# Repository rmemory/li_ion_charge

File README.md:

This repo contains the schematic and PCB layout for a battery charge controller board. 

The intent of this board is to provide a simple controller to connect a USB port to a discrete single cell recharagable Lithum Ion battery. The USB port will be used to provide power input only (~4.5v), and consequently the USB data port will not be used. This board will also be capable of providing power to a CPU board (3.3V). 

The charge controller chip selected for this board is the Microchip MCP73834. The 834 has been selected due to the optional timer functionality over the 833. The timer provides some protection to no unmonitored, unattended charging over a long period of time.

http://ww1.microchip.com/downloads/en/DeviceDoc/22005a.pdf

Its benefits include the following:

* This chip adhers to all of the power standards of the USB bus and also intended primarily to charge a lithium ion battery.

* Integrated pass (controlling) transistor. This has the advantage of not requiring a seperate external discrete part. The potential slight disadvantage of not being able to control the exact characteristics of the transistor are not a problem in this particular case.

* Integrated current sense.

* The reverse discharge protection feature is nice but in this case not a priority because only a USB connector input (4.2 - 4.5v) will be supported as opposed to two open wires (which in theory could be connected to anything allowing the battery to be discharged).

* Preconditioning of a deeply discharged battery is another nice feature to prevent overheating (and fire!) of the battery during recharge. If a Li-ion battery is deeply discharged (for example, to below 3 V) a small “pre-conditioning” charge of around 10% of the full-charge current is applied. This prevents the cell from overheating until such a time that it is able to accept the full current of the constant-current phase. In reality, this phase is rarely needed because most modern mobile devices are designed to shut down while there’s still some charge left because deep discharge, like overcharging, can damage the cell. With that said, note the external heat sensing thermistor is not used in this design.

* The sample application circuit specified in the data sheet will be used with minor modifications.

* A linear drop out mode is also useful as the internal resistance of the battery increases and battery output voltage degrades.

* The MSOP 10 package will be used to allow for hand soldering.

A designer's guide to lithium battery charging can be found here:

https://www.digikey.com/en/articles/techzone/2016/sep/a-designer-guide-fast-lithium-ion-battery-charging

Circut design notes:
======================

The "typical application" circuit provided on the data sheet will provide the core of the circuit design.

A regulated current of 500 mA will be used, and thus according to the equation Ireg = 1000V/Rprog, a value of 2k ohms for the Rprog will be used.

A standard USB Type A connector will be used. 

A slightly larger 4.7 uF capacitor, with a 1206 foot print will be used to accomodate for the 500 mA charging current. The 4.7 uF caps are available in an 0805 size, but they tend to be more expensive and more difficuclt to find.

Rudimentary reset functionality will be provided via a jumper.

Via Stitching (i.e. adding of extra vias between planes) reduces inductance between planes. All conductors have some inductance due to the magnetic field due to the current flowing. The inductance will increase as signal frequency increases. For example, a square wave (data) has many high frequency signals. One via will create a small inductor. More vias reduce the inductance by putting inductors in parallel, thus reducing overall impedance of the signals between planes, thus making sure the signal isn't distorted between planes. Via stitching also helps heat dissapation. 

General KiCad Workflow notes:
=============================

* Add parts to project specific library as needed

* Draw schematic, with values

* Annotate schematic

* Run ERC, address any critical errors

* Generate netlist

* Run CvPcb to associate parts in schematic with footprints, creating footprints where necessary

* PCBNew for layout
  * Read current net list
  * Mode Footprint button selected (third from the right in the top bar). Then right click on the stack of footprints and select "Glob Move and Place->Move All modules"

The overheating feature will not be used, and thus the thermistor will be replaced by a fixed 10k value.

BOM Generation notes:
=====================

http://og2k.com/content/how-generate-bill-materials-bom-kicad

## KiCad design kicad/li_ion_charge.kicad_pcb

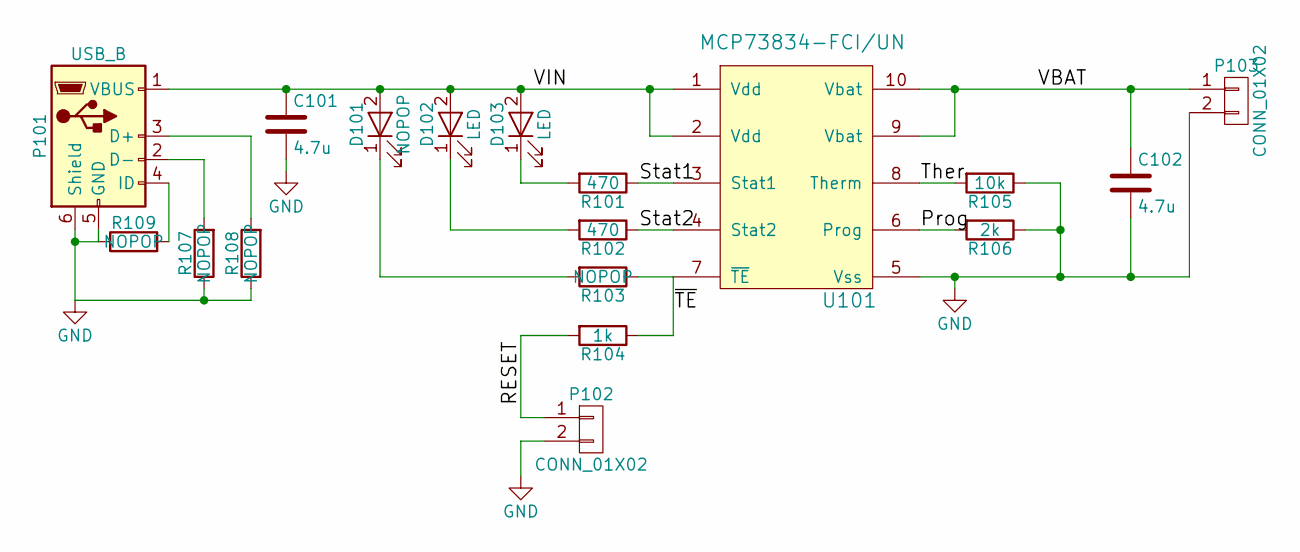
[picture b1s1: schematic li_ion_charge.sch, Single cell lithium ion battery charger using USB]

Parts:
C101, C102: 4.7u; C_1206_HandSoldering
D101: NOPOP; LED_0805
D102, D103: LED; LED_0805
P101: USB_B; USB_Micro-B_10118193-0001LF; MPN 10118193-0001LF
P102, P103: CONN_01X02; Pin_Header_Straight_1x02_Pitch2.54mm
R101, R102: 470; R_0805_HandSoldering
R103, R107, R108, R109: NOPOP; R_0805_HandSoldering
R104: 1k; R_0805_HandSoldering
R105: 10k; R_0805_HandSoldering
R106: 2k; R_0805_HandSoldering
U101: MCP73834-FCI/UN; MSOP-10_3x3mm_Pitch0.5mm

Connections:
/Prog: R106.2, U101.6 (Prog)
/RESET: P102.1, R104.2
/Stat1: R101.1, U101.3 (Stat1)
/Stat2: R102.1, U101.4 (Stat2)
/Ther: R105.2, U101.8 (Therm)
/VBAT: C102.1, P103.1, U101.9 (Vbat), U101.10 (Vbat)
/VIN: C101.1, D101.2 (A), D102.2 (A), D103.2 (A), P101.1 (VBUS), U101.1 (Vdd), U101.2 (Vdd)
/~TE: R103.1, R104.1, U101.7 (~TE)
GND: C101.2, C102.2, P101.5 (GND), P101.6 (Shield), P102.2, P103.2, R105.1, R106.1, R107.1, R108.1, R109.1, U101.5 (Vss)
unnamed: D101.1 (K), R103.2
unnamed: D102.1 (K), R102.2
unnamed: D103.1 (K), R101.2
unnamed: P101.2 (D-), R107.2
unnamed: P101.3 (D+), R108.2
unnamed: P101.4 (ID), R109.2

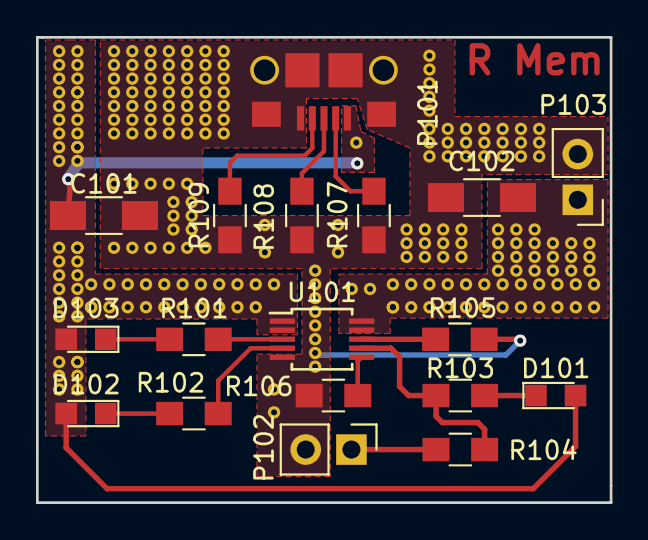
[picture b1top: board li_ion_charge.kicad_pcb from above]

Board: 2 copper layers, 31.9 x 25.9 mm, 18 parts (0 on the bottom side), 15 nets.

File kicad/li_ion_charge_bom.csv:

Reference, Value, Footprint, Datasheet, MPN
"D103","LED","LEDs:LED_0805","https://media.digikey.com/pdf/Data%20Sheets/Lite-On%20PDFs/L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","LTST-S220GKT"
"D101","NOPOP","LEDs:LED_0805",""
"D102","LED","LEDs:LED_0805","https://media.digikey.com/pdf/Data%20Sheets/Lite-On%20PDFs/L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","LTST-S220GKT"
"R102","470","Resistors_SMD:R_0805_HandSoldering","","RMCF0805JT470R"
"R103","NOPOP","Resistors_SMD:R_0805_HandSoldering",""
"R101","470","Resistors_SMD:R_0805_HandSoldering","","RMCF0805JT470R"
"U101","MCP73834","Housings_SSOP:MSOP-10_3x3mm_Pitch0.5mm","http://ww1.microchip.com/downloads/en/DeviceDoc/22005a.pdf","MCP73834-FCI/UN"
"R106","2k","Resistors_SMD:R_0805_HandSoldering","","ERJ-6ENF2001V"
"R105","10k","Resistors_SMD:R_0805_HandSoldering","","RC0805JR-0710KL"
"C102","4.7u","Capacitors_SMD:C_1206_HandSoldering","http://www.yuden.co.jp/productdata/catalog/en/mlcc_all_e.pdf","LMK316B7475KL-T"
"P103","CONN_01X02","Pin_Headers:Pin_Header_Straight_1x02_Pitch2.00mm","","M20-9990246"
"C101","4.7u","Capacitors_SMD:C_1206_HandSoldering","http://www.yuden.co.jp/productdata/catalog/en/mlcc_all_e.pdf","LMK316B7475KL-T"
"P101","USB_B","li_ion_charge_library:USB_Micro-B_10118193-0001LF","http://portal.fciconnect.com/Comergent//fci/drawing/10118193.pdf","10118193-0001LF"
"R104","1k","Resistors_SMD:R_0805_HandSoldering","","RC0805JR-071KL"
"P102","CONN_01X02","Pin_Headers:Pin_Header_Straight_1x02_Pitch2.54mm","","M20-9990246"
"R108","NOPOP","Resistors_SMD:R_0805_HandSoldering",""
"R107","NOPOP","Resistors_SMD:R_0805_HandSoldering",""
"R109","NOPOP","Resistors_SMD:R_0805_HandSoldering",""
"J101","CONN_01X02","","http://www.jst-mfg.com/product/pdf/eng/ePH.pdf","B2B-PH-K-S(LF)(SN)"

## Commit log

2017-03-04 initial commit of empty kicad project
2017-03-04 Add library for MCP73834 part and add it to schematic
2017-03-05 Add a section in the README for circuit design notes
2017-03-05 Added notes to README regarding regulated current and cap values
2017-03-05 Initial implementation of schematic with values
2017-03-05 Add KiCad workflow notes
2017-03-05 Add footprint associations usinb CvPcb
2017-03-07 Update to vertical connector footprints and start initial layout
2017-03-07 Add a more kicad notes
2017-03-07 various updates to the readme
2017-03-07 Updated comments in README
2017-03-07 Minor update to schematic after adding initial layout
2017-03-08 First iteration of complete layout
2017-03-08 Change notes on reset functionality
2017-03-08 Second iteration of the layout; added several net labels as well
2017-03-09 Add initial USB micro B footprint
2017-03-09 Add datasheet for USB to schematic
2017-03-11 change the schematic to use a micro USB part, and update netlist and layout accordingly
2017-03-12 Move everything from li_ion_charge_library.pretty to li_ion_charge_library, and remove the .pretty directory. In other words, minor organization cleanup
2017-03-12 Adjust footprint of Micro USB to match the datasheet
2017-03-12 Final USB footprint and added a label to schematic
2017-03-12 Update schematic and netlist to include a new nopop resistor, and this should be close to what the final part placement on the layout should look like
2017-03-12 First iteration of adding power planes and initial traces. Still need to add osh-park defaults and address ERC errors
2017-03-14 Add data sheet for MCP738334
2017-03-15 Add initial osh part design rule defaults
2017-03-16 Front side planes and traces added
2017-03-19 add power planes to back side
2017-03-21 cleanup of zones, added zone for power from Vin pin, and initial edge cuts of board
2017-03-22 add a couple vias
2017-03-25 add stitching via footprint
2017-03-26 Add gerbers, and order boards from Osh Park
2017-03-26 Update README.md, adding notes for via stitching.
2017-03-26 Update README.md to include notes for BOM generation
2017-03-27 initial BOM
2017-03-27 Minor schematic change
